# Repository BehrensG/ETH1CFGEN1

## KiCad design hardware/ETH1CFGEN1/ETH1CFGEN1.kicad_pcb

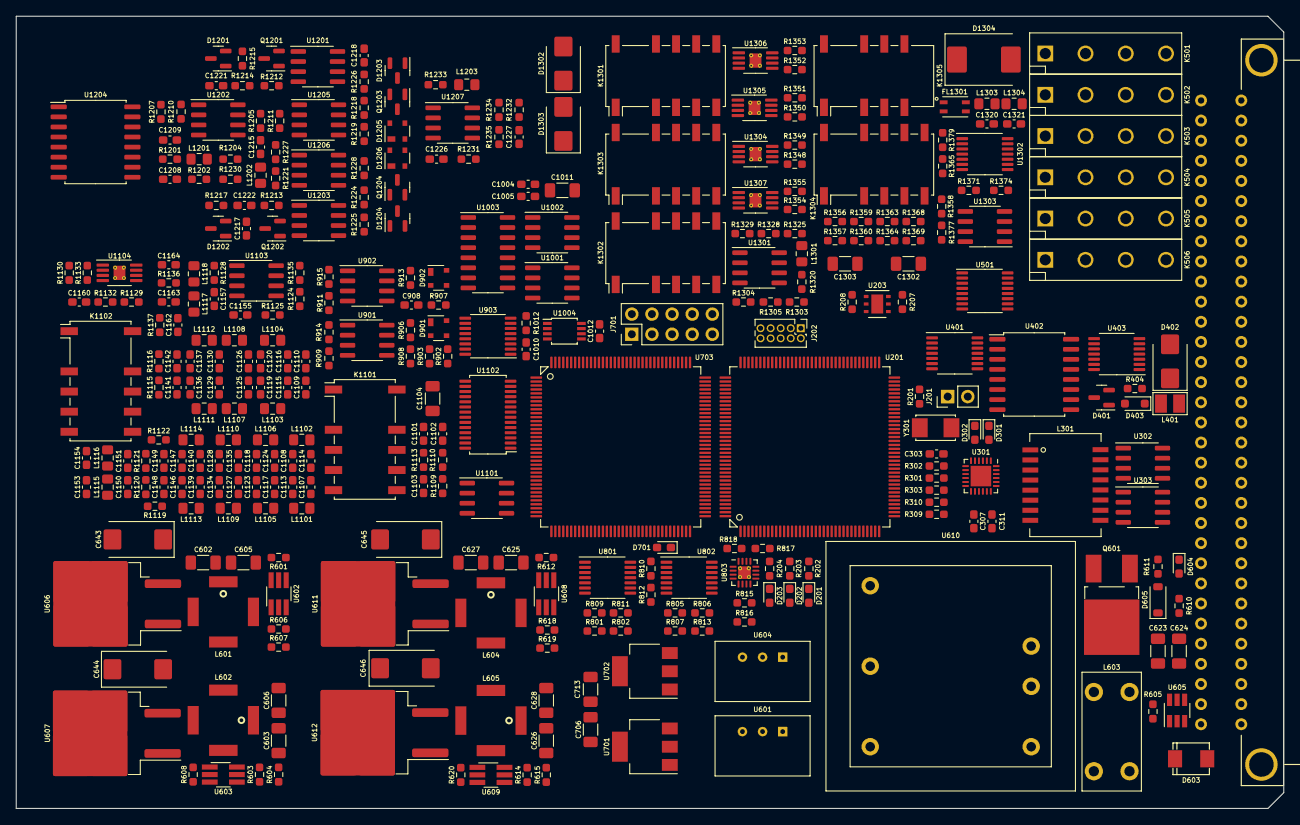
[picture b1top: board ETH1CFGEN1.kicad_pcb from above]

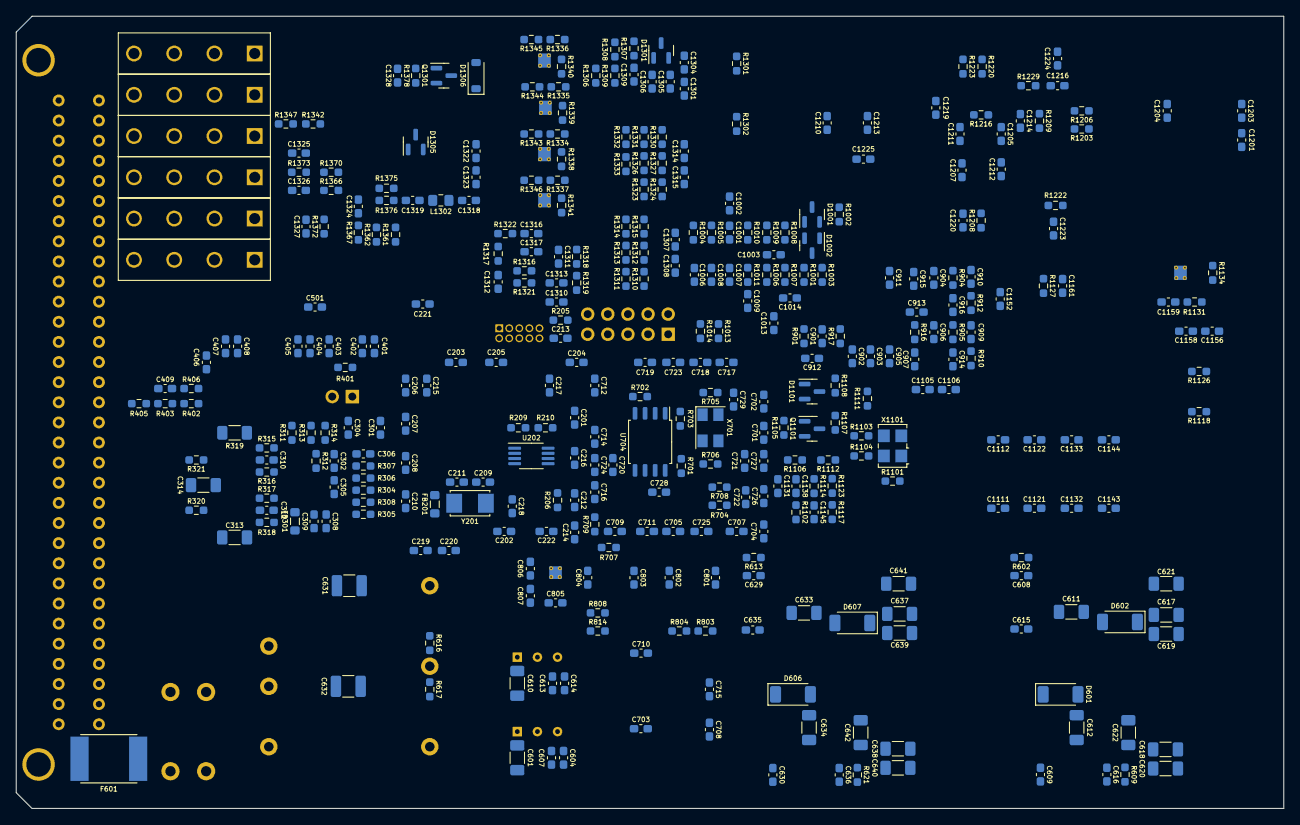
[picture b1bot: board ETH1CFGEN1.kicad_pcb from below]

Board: 6 copper layers, 160.0 x 100.0 mm, 693 parts (353 on the bottom side), 391 nets, no tracks yet.

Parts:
C201, C202, C203, C204, C205, C206, C207, C208, C210, C212, C213, C214, C216, C221, C222, C302, C305, C308, C309, C310, C311, C312, C401, C403, C404, C406, C408, C607, C614, C701, C702, C703, C704, C705, C707, C708, C709, C710, C711, C712, C714, C715, C716, C717, C718, C719, C720, C721, C722, C723, C724, C725, C726, C727, C728, C729, C801, C802, C803, C804, C806, C905, C907, C908, C913, C914, C915, C916, C1001, C1002, C1003, C1007, C1012, C1013, C1014, C1103, C1131, C1138, C1201, C1203, C1204, C1205, C1207, C1210, C1211, C1212, C1213, C1216, C1217, C1218, C1220, C1223, C1224, C1305, C1306, C1324, C1325, C1326, C1327: 100n; C_0603_1608Metric_Pad1.08x0.95mm_HandSolder
C209, C211, C301, C304: 8p; C_0603_1608Metric_Pad1.08x0.95mm_HandSolder
C215, C217: 2u2; C_0603_1608Metric_Pad1.08x0.95mm_HandSolder
C218, C219, C220, C306, C307, C402, C405, C407, C501, C604, C608, C609, C613, C629, C630, C805, C807, C1312, C1313, C1316: 1u; C_0603_1608Metric_Pad1.08x0.95mm_HandSolder
C303, C1004: 470p; C_0603_1608Metric_Pad1.08x0.95mm_HandSolder
C313, C314: 1n/1kV; C_1206_3216Metric_Pad1.33x1.80mm_HandSolder
C409, C1150, C1151, C1161: 47p; C_0603_1608Metric_Pad1.08x0.95mm_HandSolder
C601, C610: 1u/50V; C_1206_3216Metric_Pad1.33x1.80mm_HandSolder
C602, C603, C625, C626: 10u/50V; C_1206_3216Metric_Pad1.33x1.80mm_HandSolder
C605, C606, C617, C618, C619, C620, C623, C624, C627, C628, C639: 4u7/50V; C_1206_3216Metric_Pad1.33x1.80mm_HandSolder
C611, C612, C633, C634: 1u/HC; C_1206_3216Metric_Pad1.33x1.80mm_HandSolder
C615, C616, C635, C636: 4p7; C_0603_1608Metric_Pad1.08x0.95mm_HandSolder
C621, C622: 10u/35V; C_1206_3216Metric_Pad1.33x1.80mm_HandSolder
C631, C632: 330p/2kV; C_1210_3225Metric_Pad1.33x2.70mm_HandSolder
C637, C638, C640: 4u7/25V; C_1206_3216Metric_Pad1.33x1.80mm_HandSolder
C641, C642: 10u/25V; C_1206_3216Metric_Pad1.33x1.80mm_HandSolder
C643, C644, C645, C646: 22u/35V; CP_EIA-7343-31_Kemet-D_Pad2.25x2.55mm_HandSolder
C706, C713, C1104, C1302, C1303: 10u; C_1206_3216Metric_Pad1.33x1.80mm_HandSolder
C901, C912: 150n; C_0603_1608Metric_Pad1.08x0.95mm_HandSolder
C902, C903, C904, C906, C1145, C1152, C1221, C1222: 220n; C_0603_1608Metric_Pad1.08x0.95mm_HandSolder
C909, C910, C1008: 1000p; C_0603_1608Metric_Pad1.08x0.95mm_HandSolder
C911, C1317: 10n; C_0603_1608Metric_Pad1.08x0.95mm_HandSolder
C1005, C1136, C1137: 330p; C_0603_1608Metric_Pad1.08x0.95mm_HandSolder
C1006: 220p; C_0603_1608Metric_Pad1.08x0.95mm_HandSolder
C1009, C1125, C1126, C1164: 150p; C_0603_1608Metric_Pad1.08x0.95mm_HandSolder
C1010, C1208, C1214, C1215: 4700p; C_0603_1608Metric_Pad1.08x0.95mm_HandSolder
C1011: 2u2; C_1206_3216Metric_Pad1.33x1.80mm_HandSolder
C1101, C1102, C1107, C1108, C1111, C1112, C1121, C1122, C1132, C1133, C1143, C1144, C1163: 33p; C_0603_1608Metric_Pad1.08x0.95mm_HandSolder
C1105, C1106, C1146, C1147, C1156, C1158, C1301, C1304, C1307, C1308, C1314, C1315, C1322, C1323: 100p; C_0603_1608Metric_Pad1.08x0.95mm_HandSolder
C1109, C1110: 30p; C_0603_1608Metric_Pad1.08x0.95mm_HandSolder
C1113, C1114, C1117, C1118, C1123, C1124, C1141, C1142: 56p; C_0603_1608Metric_Pad1.08x0.95mm_HandSolder
C1115, C1116, C1319: 3p3; C_0603_1608Metric_Pad1.08x0.95mm_HandSolder
C1119, C1120: 120p; C_0603_1608Metric_Pad1.08x0.95mm_HandSolder
C1127, C1128, C1227: 62p; C_0603_1608Metric_Pad1.08x0.95mm_HandSolder
C1129, C1130: 8p2; C_0603_1608Metric_Pad1.08x0.95mm_HandSolder
C1134, C1135: 130p; C_0603_1608Metric_Pad1.08x0.95mm_HandSolder
C1139, C1140, C1162: 15p; C_0603_1608Metric_Pad1.08x0.95mm_HandSolder
C1148, C1149, C1226: 5p6; C_0603_1608Metric_Pad1.08x0.95mm_HandSolder
C1153, C1154, C1225: 22p; C_0603_1608Metric_Pad1.08x0.95mm_HandSolder
C1155, C1159, C1160, C1219: 10p; C_0603_1608Metric_Pad1.08x0.95mm_HandSolder
C1157: 1p; C_0603_1608Metric_Pad1.08x0.95mm_HandSolder
C1209: 3300p; C_0603_1608Metric_Pad1.08x0.95mm_HandSolder
C1309, C1310, C1311, C1328: 1n; C_0603_1608Metric_Pad1.08x0.95mm_HandSolder
C1318: 27p; C_0603_1608Metric_Pad1.08x0.95mm_HandSolder
C1320, C1321: 18p; C_0603_1608Metric_Pad1.08x0.95mm_HandSolder
D201, D701: BLUE; LED_0603_1608Metric_Pad1.05x0.95mm_HandSolder
D202, D604: RED; LED_0603_1608Metric_Pad1.05x0.95mm_HandSolder
D203, D302: GREEN; LED_0603_1608Metric_Pad1.05x0.95mm_HandSolder
D301: YELLOW; LED_0603_1608Metric_Pad1.05x0.95mm_HandSolder
D401, D1001, D1002, D1203, D1204, D1301, D1305: BAV99; SOT-23
D402: SMBJ5.0A; D_SMB
D403: SD36C-01FTG; D_SOD-323_HandSoldering
D601, D602, D606, D607: PMEG6010EP,115; D_SOD-128
D603: SM6T30AY; DO_214AA_REV
D605: MMSZ5249B; D_SOD-123
D901, D902, D1205, D1206: BAS40-07-E6327; SOT-143
D1101: BAS40-04; SOT-23
D1201, D1202: BZX84C3V0; SOT-23
D1302, D1303: SZ1SMB5918BT3G; D_SMB
D1304: SMCJ43CA; D_SMC
D1306: 1N4148; D_SOD-123
F601: MF-LSMF185/33X; Fuse_SMD2920
FB201, FB301: 742792031; L_0805_2012Metric_Pad1.05x1.20mm_HandSolder
FL1301: ACP3225-102-2P-T000; ACP3225
J201: Conn_02x01; PinHeader_1x02_P2.54mm_Vertical
J202: 20021111-00010T4LF; PinHeader_2x05_P1.27mm_Vertical
J501: C64AC; Socket_DIN41612-CaseC1-AC-Male-64Pin-2rows
J701: Conn_02x05_Odd_Even; PinHeader_2x05_P2.54mm_Vertical
K501, K502, K503, K504, K505, K506: HE3621A0510; HE360_x-5050462-8
K1101, K1102, K1301, K1302, K1303, K1304: G6SU-2F-DC3; Relay_DPDT_Omron_G6SK-2F
K1305: TX2SA-4.5V; Relay_DPDT_Omron_G6S-2F
L301: 749010012A
L401: CW252016-R33G; CW252016
L601, L602, L604, L605: 74489440068
L603: 7448014501
L1101, L1102, L1103, L1104, L1105, L1106: 470n; L_0805_2012Metric_Pad1.15x1.40mm_HandSolder
L1107, L1108: 680n; L_0805_2012Metric_Pad1.15x1.40mm_HandSolder
L1109, L1110: 560n; L_0805_2012Metric_Pad1.15x1.40mm_HandSolder
L1111, L1112: 910n; L_0805_2012Metric_Pad1.15x1.40mm_HandSolder
L1113, L1114: 750n; L_0805_2012Metric_Pad1.15x1.40mm_HandSolder
L1115, L1116: 1u; L_0805_2012Metric_Pad1.15x1.40mm_HandSolder
L1117: 1u2; L_0805_2012Metric_Pad1.15x1.40mm_HandSolder
L1118: 100n; L_0805_2012Metric_Pad1.15x1.40mm_HandSolder
L1201, L1301: 1m; L_0805_2012Metric_Pad1.15x1.40mm_HandSolder
L1202, L1203: 82n; L_0805_2012Metric_Pad1.15x1.40mm_HandSolder
L1302: 180n; L_0805_2012Metric_Pad1.15x1.40mm_HandSolder
L1303, L1304: 47n; L_0805_2012Metric_Pad1.15x1.40mm_HandSolder
Q601: IRFR5410; TO-252-2_Rectifier
Q1101, Q1203: MMBT5087LT1G; SOT-23
Q1201: MMBF4416A; SOT-23
Q1202: MMBFJ175LT1; SOT-23
Q1204: MMBT6429LT1; SOT-23
Q1301: 2N7002; SOT-23
R201, R205, R206, R303, R306, R307, R308, R309, R311, R401, R701, R702, R709, R913, R916, R1001, R1002, R1003, R1004, R1005, R1006, R1007, R1013, R1102, R1117, R1123, R1127, R1203, R1206, R1210, R1225, R1226, R1232, R1303, R1319, R1377, R1378: 10k; R_0603_1608Metric_Pad0.98x0.95mm_HandSolder
R202, R204: 680; R_0603_1608Metric_Pad0.98x0.95mm_HandSolder
R203: 560; R_0603_1608Metric_Pad0.98x0.95mm_HandSolder
R207, R208, R209, R210, R704, R708, R817, R818: 4k7; R_0603_1608Metric_Pad0.98x0.95mm_HandSolder
R301, R302, R304, R305: 33; R_0603_1608Metric_Pad0.98x0.95mm_HandSolder
R310: 1k5; R_0603_1608Metric_Pad0.98x0.95mm_HandSolder
R312: 12k1; R_0603_1608Metric_Pad0.98x0.95mm_HandSolder
R313, R314: 270; R_0603_1608Metric_Pad0.98x0.95mm_HandSolder
R315, R316, R317, R318: 49R9; R_0603_1608Metric_Pad0.98x0.95mm_HandSolder
R319: 1M/1kV; R_1206_3216Metric_Pad1.30x1.75mm_HandSolder
R320, R321: 75/1%; R_0603_1608Metric_Pad0.98x0.95mm_HandSolder
R402: 14k7; R_0603_1608Metric_Pad0.98x0.95mm_HandSolder
R403, R1105, R1115, R1116, R1119, R1122, R1125, R1212, R1213, R1220, R1222: 100; R_0603_1608Metric_Pad0.98x0.95mm_HandSolder
R404, R705, R809, R810, R811, R812, R902, R903, R904, R905, R907, R917, R1014, R1101, R1107, R1114, R1207, R1308: 1k; R_0603_1608Metric_Pad0.98x0.95mm_HandSolder
R405: 47; R_0603_1608Metric_Pad0.98x0.95mm_HandSolder
R406, R1103, R1104, R1128, R1135, R1342, R1347: 51R1; R_0603_1608Metric_Pad0.98x0.95mm_HandSolder
R601, R603, R606, R608, R612, R614, R618, R620: 1M; R_0603_1608Metric_Pad0.98x0.95mm_HandSolder
R602, R604, R613, R615: 287k; R_0603_1608Metric_Pad0.98x0.95mm_HandSolder
R605, R914, R915, R1131, R1134, R1204, R1218, R1231, R1304, R1307, R1358, R1362, R1365, R1366: 100k; R_0603_1608Metric_Pad0.98x0.95mm_HandSolder
R607: 97k6; R_0603_1608Metric_Pad0.98x0.95mm_HandSolder
R609, R1379: 46k4; R_0603_1608Metric_Pad0.98x0.95mm_HandSolder
R610: 6k8; R_0603_1608Metric_Pad0.98x0.95mm_HandSolder
R611: 370; R_0603_1608Metric_Pad0.98x0.95mm_HandSolder
R616, R617: OPT; R_0603_1608Metric_Pad0.98x0.95mm_HandSolder
R619, R802, R806: 249k; R_0603_1608Metric_Pad0.98x0.95mm_HandSolder
R621: 111k; R_0603_1608Metric_Pad0.98x0.95mm_HandSolder
R703: 2k2; R_0603_1608Metric_Pad0.98x0.95mm_HandSolder
R706: 27; R_0603_1608Metric_Pad0.98x0.95mm_HandSolder
R707: 1K; R_0603_1608Metric_Pad0.98x0.95mm_HandSolder
R801, R805, R813: 33k; R_0603_1608Metric_Pad0.98x0.95mm_HandSolder
R803, R804, R807, R808, R814: 49k9; R_0603_1608Metric_Pad0.98x0.95mm_HandSolder
R815, R901, R1216: 0; R_0603_1608Metric_Pad0.98x0.95mm_HandSolder
R816: DNP; R_0603_1608Metric_Pad0.98x0.95mm_HandSolder
R906, R908: 1k96; R_0603_1608Metric_Pad0.98x0.95mm_HandSolder
R909, R911: 24k9; R_0603_1608Metric_Pad0.98x0.95mm_HandSolder
R910, R912: 33k2; R_0603_1608Metric_Pad0.98x0.95mm_HandSolder
R1008, R1010, R1011: 6k81; R_0603_1608Metric_Pad0.98x0.95mm_HandSolder
R1009: 237k; R_0603_1608Metric_Pad0.98x0.95mm_HandSolder
R1012, R1209, R1211: 619; R_0603_1608Metric_Pad0.98x0.95mm_HandSolder
R1106: 82k5; R_0603_1608Metric_Pad0.98x0.95mm_HandSolder
R1108: 2k; R_0603_1608Metric_Pad0.98x0.95mm_HandSolder
R1109, R1113: 69; R_0603_1608Metric_Pad0.98x0.95mm_HandSolder
R1110, R1111: 261; R_0603_1608Metric_Pad0.98x0.95mm_HandSolder
R1112, R1301, R1302: 21k5; R_0603_1608Metric_Pad0.98x0.95mm_HandSolder
R1118, R1126: 1k78; R_0603_1608Metric_Pad0.98x0.95mm_HandSolder
R1120, R1121: 511; R_0603_1608Metric_Pad0.98x0.95mm_HandSolder
R1124, R1219, R1223, R1224, R1228, R1338, R1339, R1340, R1341, R1356, R1357, R1359, R1360, R1363, R1364, R1368, R1369: 21R5; R_0603_1608Metric_Pad0.98x0.95mm_HandSolder
R1129, R1130: 200; R_0603_1608Metric_Pad0.98x0.95mm_HandSolder
R1132, R1133: 953; R_0603_1608Metric_Pad0.98x0.95mm_HandSolder
R1136, R1235, R1306, R1309: 34R8; R_0603_1608Metric_Pad0.98x0.95mm_HandSolder
R1137: 196; R_0603_1608Metric_Pad0.98x0.95mm_HandSolder
R1201: 348; R_0603_1608Metric_Pad0.98x0.95mm_HandSolder
R1202, R1334, R1335, R1336, R1337: 178; R_0603_1608Metric_Pad0.98x0.95mm_HandSolder
R1205: 1k47; R_0603_1608Metric_Pad0.98x0.95mm_HandSolder
R1208, R1215: 2k05; R_0603_1608Metric_Pad0.98x0.95mm_HandSolder
R1214, R1217: 5k11; R_0603_1608Metric_Pad0.98x0.95mm_HandSolder
R1221, R1227, R1233, R1234: 316; R_0603_1608Metric_Pad0.98x0.95mm_HandSolder
R1229, R1230: 500; R_0603_1608Metric_Pad0.98x0.95mm_HandSolder
R1305: 12k4; R_0603_1608Metric_Pad0.98x0.95mm_HandSolder
R1310, R1311, R1314, R1315, R1323, R1324, R1330, R1331, R1332, R1333: 383; R_0603_1608Metric_Pad0.98x0.95mm_HandSolder
R1312, R1313, R1326, R1327: 287; R_0603_1608Metric_Pad0.98x0.95mm_HandSolder
R1316: 45k3; R_0603_1608Metric_Pad0.98x0.95mm_HandSolder
R1317, R1318, R1320, R1321: 10; R_0603_1608Metric_Pad0.98x0.95mm_HandSolder
R1322: 31R6; R_0603_1608Metric_Pad0.98x0.95mm_HandSolder
R1325, R1328, R1329: 162; R_0603_1608Metric_Pad0.98x0.95mm_HandSolder
R1343, R1344, R1345, R1346: 909; R_0603_1608Metric_Pad0.98x0.95mm_HandSolder
R1348, R1349, R1350, R1351, R1352, R1353, R1354, R1355: 56R2; R_0603_1608Metric_Pad0.98x0.95mm_HandSolder
R1361: 3k48; R_0603_1608Metric_Pad0.98x0.95mm_HandSolder
R1367, R1372: 59k; R_0603_1608Metric_Pad0.98x0.95mm_HandSolder
R1370, R1371: 215k; R_0603_1608Metric_Pad0.98x0.95mm_HandSolder
R1373, R1374: 5k62; R_0603_1608Metric_Pad0.98x0.95mm_HandSolder
R1375: 30k1; R_0603_1608Metric_Pad0.98x0.95mm_HandSolder
R1376: 19k6; R_0603_1608Metric_Pad0.98x0.95mm_HandSolder
U201: STM32H723ZGTx; TQFP-144_20x20mm_P0.5mm
U202: 24LC08B-E/MS; MSOP-8_3x3mm_P0.65mm
U203: HDC1080; Texas_PWSON-N6
U301: LAN8742; QFN-24-1EP_4x4mm_P0.5mm_EP2.6x2.6mm
U302, U303: LC03-3.3BTG; SOIC-8_3.9x4.9mm_P1.27mm
U401: TXB0104PW; TSSOP-14_4.4x5mm_P0.65mm
U402: ADuM5402; SOIC-16W_7.5x10.3mm_P1.27mm
U403: 74AC125; TSSOP-14_4.4x5mm_P0.65mm
U501: ULN2003AIPWR; TSSOP-16_4.4x5mm_P0.65mm
U601: TSR1-2450; TSR1
U602, U603, U608, U609: LT8330ES6#TRMPBF; TSOT-23-6_HandSoldering
U604: TSR1-2433; TSR1
U605: MAX5902AAEUT+T; SOT-23-6_Handsoldering
U606: MC7815BD2TR4G; TO-263-2
U607: MC7915ACD2TG; TO-263-2
U610: THL15-2415WI; THL15
U611: MC7805CD2TG; TO-263-2
U612: L7905CD2T-TR; TO-263-2
U701: TLV1117LV33DCYR; SOT-223-3_TabPin2
U702: TLV1117LV12DCYR; SOT-223-3_TabPin2
U703: XC6SLX9-3TQG144I; TQFP-144_20x20mm_P0.5mm
U704: W25Q64JV; SOIC-8_5.23x5.23mm_P1.27mm
U801, U802: TL074HIPWR; TSSOP-14_4.4x5mm_P0.65mm
U803: TLA2528IRTER; WQFN-16-1EP_3x3mm_P0.5mm_EP1.6x1.6mm_ThermalVias
U901, U902, U1001, U1002, U1301, U1303: TL072CD; SOIC-8_3.9x4.9mm_P1.27mm
U903: DAC8568IBPW; TSSOP-16_4.4x5mm_P0.65mm
U1003: DG408DY-T1-E3; SOIC-16_3.9x9.9mm_P1.27mm
U1004: ADS7818EB; TSSOP-8_3x3mm_P0.65mm
U1101: TL072CDT; SOIC-8_3.9x4.9mm_P1.27mm
U1102: AD9744; TSSOP-28_4.4x9.7mm_P0.65mm
U1103: LT1016CS8; SOIC-8_3.9x4.9mm_P1.27mm
U1104, U1304, U1305, U1306, U1307: THS3001IDG; MSOP-8-1EP_3x3mm_P0.65mm_EP1.5x1.8mm_ThermalVias
U1201, U1202, U1203: AD706ARZ; SOIC-8_3.9x4.9mm_P1.27mm
U1204: AD1851RZ; SOIC-16W_7.5x10.3mm_P1.27mm
U1205: AD8180ARZ; SOIC-8_3.9x4.9mm_P1.27mm
U1206, U1207: AD8009AR; SOIC-8_3.9x4.9mm_P1.27mm
U1302: LMV339IPWR; TSSOP-14_4.4x5mm_P0.65mm
X701: ASFL1-100.000MHZ-L-T; Crystal_SMD_5032-4Pin_5.0x3.2mm
X1101: SG5032CAN 50.000000M-TJGA3; Oscillator_SMD_SeikoEpson_SG8002LB-4Pin_5.0x3.2mm
Y201: NX5032GA-16.000M; NX5032GA
Y301: NX5032GA-25.000000MHZ-LN-CD-1; NX5032GA

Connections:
+2V5: R901.1, R909.1, R911.1, R1003.2, R1004.1, R1009.2, R1117.1, R1208.1, R1303.1, U1002.1, U1002.2 (-), U1302.11 (+)
+3.3V: C201.1, C202.1, C203.1, C204.1, C205.1, C206.1, C207.1, C208.1, C210.1, C212.1, C214.1, C216.1, C218.1, C221.2, C222.2, C302.1, C305.1, C401.1, C402.1, C613.1, C614.1, C806.2, C912.2, D201.2 (A), D202.2 (A), D203.2 (A), D1101.2, FB201.2, FB301.2, J202.1, R201.2, R205.1, R207.1, R208.1, R209.1, R210.1, R306.1, R307.1, R308.1, R309.1, R310.1, R401.1, R817.1, R818.1, R1101.1, R1107.2, U201.6 (VBAT), U201.17 (VDD), U201.30 (VDD), U201.39 (VDD), U201.52 (VDD), U201.62 (VDD), U201.72 (VDD), U201.84 (VDD), U201.95 (VDD33USB), U201.108 (VDD), U201.121 (VDD), U201.131 (VDD), U201.143 (PDR_ON), U201.144 (VDD), U202.8 (VCC), U203.5 (VCC), U301.9 (VDDIO), U401.1 (VCCA), U604.3 (VO), U802.3 (+), U803.10 (DVDD), U903.3 (AVDD), U1102.24 (AVDD), U1102.27 (DVDD), X1101.4 (VCC)
+5V: C403.1, C404.1, C405.1, C641.1, C645.1, C805.2, C1012.1, C1201.1, C1204.1, C1205.1, C1207.1, C1210.1, D1306.1 (K), K1305.1, R805.2, R1002.1, R1013.1, U401.14 (VCCB), U402.1 (VDD1), U611.3 (OUT), U803.7 (AVDD), U1004.8 (VDD), U1103.1 (V+), U1204.3 (+Vl), U1204.16 (+VS), U1205.4 (+VS), U1206.7 (V+), U1207.7 (V+)
+5VD: C501.1, C604.1, C607.1, C703.1, K501.2, K502.2, K503.2, K504.2, K505.2, K506.2, R813.2, U501.9 (COM), U601.3 (VO), U701.3 (VI)
+5VP: C406.1, C407.1, C408.1, R404.1, U402.10 (VSEL), U402.16 (VISO), U403.14 (VCC)
+15V: C621.1, C643.1, C801.2, C803.2, C913.1, C915.1, C1002.1, C1007.1, C1303.1, D1001.1 (K), D1001.3 (K), D1305.2 (A), R806.2, R1112.2, R1301.1, R1366.1, U606.3 (OUT), U801.4 (V+), U802.4 (V+), U901.8 (V+), U902.8 (V+), U1001.8 (V+), U1002.8 (V+), U1101.8 (V+), U1104.7 (V+), U1201.8 (V+), U1202.8 (V+), U1203.8 (V+), U1301.8 (V+), U1302.3 (V+), U1303.8 (V+), U1304.7 (V+), U1305.7 (V+), U1306.7 (V+), U1307.7 (V+)
+24V: F601.2, J501.A31 (31A), J501.A32 (32A), J501.C31 (31C), J501.C32 (32C)
-2V5: C1001.2, R1005.2, R1006.2, U1002.7, U1302.8 (-)
-5V: C642.1, C646.2, C1203.1, C1211.1, C1212.1, C1213.1, R801.2, U612.3 (VO), U1103.4 (V-), U1204.1 (-Vs), U1205.5 (-VS), U1206.4 (V-), U1207.4 (V-)
-15V: C622.1, C644.2, C802.2, C804.2, C914.1, C916.1, C1003.1, C1014.1, C1302.1, D1002.2 (A), D1002.3 (K), D1305.1 (K), Q1101.3 (C), R802.2, R1302.2, R1365.1, U607.3 (VO), U801.11 (V-), U802.11 (V-), U901.4 (V-), U902.4 (V-), U1001.4 (V-), U1002.4 (V-), U1101.4 (V-), U1104.4 (V-), U1104.9 (THR), U1201.4 (V-), U1202.4 (V-), U1203.4 (V-), U1301.4 (V-), U1302.12 (V-), U1303.4 (V-), U1304.4 (V-), U1304.9 (THR), U1305.4 (V-), U1305.9 (THR), U1306.4 (V-), U1306.9 (THR), U1307.4 (V-), U1307.9 (THR)
/ADC/+1.25VREF: R1001.1, R1003.1, U1003.11 (S5)
/Connector/A: J501.A2 (2A), J501.C2 (2C), K501.4
/Connector/B: J501.A3 (3A), J501.C3 (3C), K502.4
/Connector/C: J501.A4 (4A), J501.C4 (4C), K503.4
/Connector/CXN_REL1: U201.88 (PG3), U501.1 (I1)
/Connector/CXN_REL2: U201.89 (PG4), U501.2 (I2)
/Connector/CXN_REL3: U201.90 (PG5), U501.3 (I3)
/Connector/CXN_REL4: U201.91 (PG6), U501.4 (I4)
/Connector/CXN_REL5: U201.92 (PG7), U501.5 (I5)
/Connector/CXN_REL6: U201.93 (PG8), U501.6 (I6)
/Connector/D: J501.A5 (5A), J501.C5 (5C), K504.4
/Connector/E: J501.A6 (6A), J501.C6 (6C), K505.4
/Connector/EXT_TRIG: C409.1, D403.1 (A1), J501.A16 (16A), L401.1
/Connector/F: J501.A7 (7A), J501.C7 (7C), K506.4
/Connector/MAIN_OUTPUT: C1321.1, D1304.2 (A2), K501.1, K502.1, L1304.2
/Connector/RX+: J501.A20 (20A), U303.8
/Connector/RX-: J501.A21 (21A), U303.5
/Connector/TX+: J501.C20 (20C), U302.8
/Connector/TX-: J501.C21 (21C), U302.5
/DAC/V_AMPL: C905.2, R916.1, U901.6 (-), U901.7
/DAC/V_NEDGE: C903.1, R903.2
/DAC/V_NULL_SINE: C909.2, R914.2, U901.1
/DAC/V_NULL_SQ: C910.2, R915.2, U902.1
/DAC/V_OFFSET: C911.1, R913.2
/DAC/V_PEDGE: C902.1, R902.2
/Ethernet/ETH_RXN: L301.8 (RD-), R318.2, U301.22 (RXN)
/Ethernet/ETH_RXP: L301.6 (RD+), R317.2, U301.23 (RXP)
/Ethernet/ETH_TXN: L301.3 (TD-), R316.2, U301.20 (TXN)
/Ethernet/ETH_TXP: L301.1 (TD+), R315.2, U301.21 (TXP)
/Ethernet/MDIO: R310.2, U201.36 (PA2), U301.12 (MDIO)
/Ethernet/MODE0: R301.1, R306.2, U301.8 (RXD0/MODE0)
/Ethernet/MODE1: R302.1, R307.2, U301.7 (RXD1/MODE1)
/Ethernet/MODE2: R304.1, R308.2, U301.11 (CRS_DV/MODE2)
/Ethernet/REFCLK0: R305.1, R309.2, U301.14 (~INT/REFCLK0)
/Ethernet/REF_CLK: R305.2, U201.35 (PA1)
/Ethernet/RMII_CRS_DV: R304.2, U201.43 (PA7)
/Ethernet/RMII_MDC: U201.27 (PC1), U301.13 (MDC)
/Ethernet/RMII_RXD0: R301.2, U201.44 (PC4)
/Ethernet/RMII_RXD1: R302.2, U201.45 (PC5)
/Ethernet/RMII_TXD0: U201.128 (PG13), U301.17 (TXD0)
/Ethernet/RMII_TXD1: U201.74 (PB13), U301.18 (TXD1)
/Ethernet/RMII_TXEN: U201.126 (PG11), U301.16 (TXEN)
/FPGA/CMPCS_B_2: R709.1, U703.72 (CMPCS_B_2)
/FPGA/DONE_2: R707.1, U703.71 (DONE_2)
/FPGA/FLASH_HOLD: R701.2, U704.7 (IO3)
/FPGA/FLASH_INIT_B: R704.2, U703.39 (IO_L65P_INIT_B_2)
/FPGA/FLASH_SCK: U703.70 (IO_L1P_CCLK_2), U704.6 (CLK)
/FPGA/FLASH_WP: R702.2, U704.3 (IO2)
/FPGA/FLASH_nCS: R703.2, U703.38 (IO_L65N_CSO_B_2), U704.1 (~CS)
/FPGA/FPGA_TCK: J701.6, U703.109 (TCK)
/FPGA/FPGA_TDI: J701.10, U703.110 (TDI)
/FPGA/FPGA_TDO: J701.8, U703.106 (TDO)
/FPGA/FPGA_TMS: J701.4, U703.107 (TMS)
/FPGA/PROG_B_2: R708.1, U703.37 (PROGRAM_B_2)
/MCU/EEPROM_WP: U201.135 (PB5), U202.7 (WP)
/MCU/I2C1_SCL: R207.2, R210.2, U201.136 (PB6), U202.6 (SCL), U203.6 (SCL)
/MCU/I2C1_SDA: R208.2, R209.2, U201.137 (PB7), U202.5 (SDA), U203.1 (SDA)
/MCU/I2C2_SCL: R817.2, U201.11 (PF1), U803.13 (SCL)
/MCU/I2C2_SDA: R818.2, U201.10 (PF0), U803.14 (SDA)
/MCU/LED_BLUE: R202.1, U201.142 (PE1)
/MCU/LED_GREEN: R204.1, U201.46 (PB0)
/MCU/LED_RED: R203.1, U201.75 (PB14)
/MCU/MCU_DEFAULT: J201.1, R201.1, U201.76 (PB15)
/MCU/NRST: C213.1, J202.10, R205.2, U201.25 (NRST), U301.15 (~RST)
/MCU/TCK_SWCLK: J202.4, U201.109 (PA14(JTCK)
/MCU/TMS_SWDIO: J202.2, U201.105 (PA13(JTMS)
/MCU/TRIG_EN: U201.102 (PA10), U401.2 (A1)
/MCU/TRIG_IN: U201.100 (PA8), U401.4 (A3)
/MCU/TRIG_OUT: U201.101 (PA9), U401.3 (A2)
/Output/MEAS_BUF: C1309.1, R1307.2
/Output/MEAS_OUT: C1328.1, R1378.2
/Output/OUTPUT: FL1301.1, K1305.8
/Output/RST_+20DB: C1322.1, K1304.12
/Output/RST_-10DB: C1308.2, K1302.1
/Output/RST_-20DB: C1315.2, K1303.1
/Output/SET_+20DB: C1323.2, K1304.1
/Output/SET_-10DB: C1307.1, K1302.12
/Output/SET_-20DB: C1314.1, K1303.12
/Output/SET_SIN_ARB: C1304.2, K1301.12
/Output/SET_SQ_PLS: C1301.1, K1301.1
/Self test/AIN0: U802.1, U802.2 (-), U803.15 (AIN0/GPIO0)
/Self test/AIN1: U802.6 (-), U802.7, U803.16 (AIN1/GPIO1)
/Self test/AIN2: R811.1, U801.1, U803.1 (AIN2/GPIO2)
/Self test/AIN3: U802.8, U802.9 (-), U803.2 (AIN3/GPIO3)
/Self test/AIN4: U802.13 (-), U802.14, U803.3 (AIN4/GPIO4)
/Self test/AIN5: R812.1, U801.8, U803.4 (AIN5/GPIO5)
/Square/SQ_PLS: C1227.1, R1235.2
/Trigger/EXT_TRIG_SIGN: R402.1, U402.12 (VIC), U403.3 (O)
/Trigger/TRIG_OUT_EN: U402.14 (VOA), U403.4 (EN), U403.10 (EN), U403.13 (EN)
/Trigger/TRIG_OUT_SIGN: U402.13 (VOB), U403.5 (D), U403.9 (D), U403.12 (D)
/WaveformDAC/SET_ARB_FLTR1: C1105.1, K1101.12
/WaveformDAC/SET_ARB_FLTR2: C1156.1, K1102.1
/WaveformDAC/SET_SIN_FLTR1: C1106.2, K1101.1
/WaveformDAC/SET_SIN_FLTR2: C1158.2, K1102.12
/WaveformDAC/SINE_ARB: C1164.1, L1118.2
/WaveformDAC/V_AMPL: D1101.3, R1102.1, U1102.17 (REFIO)
/WaveformDAC/V_DTY_CYCL: C1131.1, C1138.1, R1114.1
/WaveformDAC/WFDAC_CLK: R1103.2, U1102.28 (CLK)
Earth: C313.1, C314.2, J501.A18 (18A), J501.A22 (22A), J501.C18 (18C), J501.C22 (22C), R319.1
FPGA_1V2: C713.1, C715.1, C723.1, C724.1, C725.1, C726.1, C727.1, U702.2 (VO), U703.19 (VCCINT), U703.28 (VCCINT), U703.52 (VCCINT), U703.89 (VCCINT), U703.128 (VCCINT)
FPGA_3V3: C701.1, C702.1, C704.1, C705.1, C706.1, C707.1, C708.1, C709.1, C710.1, C711.1, C712.1, C714.1, C716.1, C717.1, C718.1, C719.1, C720.1, C721.1, C722.1, C728.1, C729.1, D701.2 (A), J701.2, R701.1, R702.1, R703.1, R704.1, R705.1, R708.2, R709.2, U701.2 (VO), U702.3 (VI), U703.4 (VCCO_3), U703.18 (VCCO_3), U703.20 (VCCAUX), U703.31 (VCCO_3), U703.36 (VCCAUX), U703.42 (VCCO_2), U703.53 (VCCAUX), U703.63 (VCCO_2), U703.69 (IO_L1N_M0_CMPMISO_2), U703.76 (VCCO_1), U703.86 (VCCO_1), U703.90 (VCCAUX), U703.103 (VCCO_1), U703.122 (VCCO_0), U703.125 (VCCO_0), U703.129 (VCCAUX), U703.135 (VCCO_0), U704.8 (VCC), X701.4 (VCC)
GND1: C406.2, C407.2, C408.2, D401.1 (K), D402.2 (A), D403.2 (A2), J501.C16 (16C), R406.2, U402.9 (GNDISO), U402.15 (GNDISO), U403.1 (EN), U403.7 (GND)
GNDA: C201.2, C202.2, C203.2, C204.2, C205.2, C206.2, C207.2, C208.2, C209.2, C210.2, C211.2, C212.2, C213.2, C214.2, C215.2, C216.2, C217.2, C218.2, C219.2, C220.2, C221.1, C222.1, C301.2, C302.2, C303.2, C304.2, C305.2, C306.2, C307.2, C308.2, C309.2, C310.2, C311.2, C312.2, C313.2, C401.2, C402.2, C403.2, C404.2, C405.2, C501.2, C601.2, C602.2, C603.2, C604.2, C605.2, C606.2, C607.2, C608.2, C609.2, C610.2, C613.2, C614.2, C617.2, C618.2, C619.2, C620.2, C621.2, C622.2, C625.2, C626.2, C627.2, C628.2, C629.2, C630.2, C632.1, C637.2, C638.2, C639.2, C640.2, C641.2, C642.2, C643.2, C644.1, C645.2, C646.1, C701.2, C702.2, C703.2, C704.2, C705.2, C706.2, C707.2, C708.2, C709.2, C710.2, C711.2, C712.2, C713.2, C714.2, C715.2, C716.2, C717.2, C718.2, C719.2, C720.2, C721.2, C722.2, C723.2, C724.2, C725.2, C726.2, C727.2, C728.2, C729.2, C801.1, C802.1, C803.1, C804.1, C805.1, C806.1, C807.1, C901.1, C902.2, C903.2, C904.2, C906.2, C907.2, C908.2, C911.2, C912.1, C913.2, C914.2, C915.2, C916.2, C1002.2, C1003.2, C1004.2, C1005.2, C1007.2, C1009.2, C1010.2, C1011.2, C1012.2, C1013.2, C1014.2, C1101.2, C1102.2, C1103.2, C1104.2, C1105.2, C1106.1, C1107.2, C1108.1, C1109.2, C1110.1, C1113.2, C1114.1, C1115.2, C1116.1, C1117.2, C1118.1, C1119.2, C1120.1, C1123.2, C1124.1, C1125.2, C1126.1, C1127.2, C1128.1, C1129.2, C1130.1, C1131.2, C1134.2, C1135.1, C1136.2, C1137.1, C1139.2, C1140.1, C1141.2, C1142.1, C1145.2, C1146.2, C1147.1, C1148.2, C1149.1, C1150.2, C1151.1, C1152.2, C1153.2, C1154.1, C1156.2, C1158.1, C1159.1, C1160.2, C1161.2, C1162.2, C1163.2, C1164.2, C1201.2, C1203.2, C1204.2, C1205.2, C1207.2, C1208.2, C1209.2, C1210.2, C1211.2, C1212.2, C1213.2, C1214.2, C1215.2, C1219.2, C1223.2, C1224.2, C1225.2, C1226.2, C1227.2, C1301.2, C1302.2, C1303.2, C1304.1, C1305.2, C1306.2, C1307.2, C1308.1, C1309.2, C1312.2, C1313.2, C1314.2, C1315.1, C1316.2, C1317.2, C1318.2, C1319.2, C1322.2, C1323.1, C1324.2, C1325.2, C1326.2, C1328.2, D601.1 (K), D606.1 (K), D1101.1, D1203.1 (K), D1204.2 (A), D1302.2 (A), D1303.1 (K), FL1301.2, J201.2, J202.3, J202.5, J701.1, J701.3, J701.5, J701.7, J701.9, K505.1, K506.1, K1301.5, K1305.3, K1305.4, K1305.5, L601.3, L604.3, L1115.2, L1116.1, L1202.2, L1203.2, Q1301.2 (S), R206.1, R303.2, R311.2, R312.1, R313.2, R314.2, R319.2, R602.2, R604.2, R607.2, R609.2, R613.2, R615.2, R617.2, R619.2, R621.2, R803.2, R804.2, R807.2, R808.2, R814.2, R816.1, R910.1, R912.1, R1001.2, R1108.1, R1115.2, R1116.1, R1120.2, R1121.1, R1132.2, R1202.1, R1203.1, R1207.2, R1215.1, R1216.1, R1218.1, R1231.1, R1304.2, R1305.2, R1310.1, R1311.1, R1314.2, R1315.2, R1323.1, R1324.1, R1330.2, R1331.2, R1332.2, R1333.2, R1334.1, R1335.1, R1336.1, R1337.1, R1367.2, R1373.2, R1374.2, R1376.2, U201.16 (VSS), U201.31 (VSSA), U201.38 (VSS), U201.51 (VSS), U201.61 (VSS), U201.83 (VSS), U201.94 (VSS), U201.107 (VSS), U201.120 (VSS), U201.130 (VSS), U202.1 (A0), U202.2 (A1), U202.3 (A2), U202.4 (GND), U203.2 (GND), U301.25 (VSS), U401.7 (GND), U402.2 (GND1), U402.8 (GND1), U501.8 (GND), U601.2 (GND), U602.2 (GND), U603.2 (GND), U604.2 (GND), U606.2 (GND), U607.1 (GND), U608.2 (GND), U609.2 (GND), U610.5 (-VOUT), U611.2 (GND), U612.1 (GND), U701.1 (GND), U702.1 (GND), U703.3 (GND), U703.13 (GND), U703.25 (GND), U703.49 (GND), U703.54 (GND), U703.60 (IO_L13P_M1_2), U703.68 (GND), U703.73 (SUSPEND), U703.77 (GND), U703.91 (GND), U703.96 (GND), U703.108 (GND), U703.113 (GND), U703.130 (GND), U703.136 (GND), U704.4 (GND), U801.3 (+), U801.10 (+), U803.9 (GND), U803.17 (PAD), U902.5 (+), U903.14 (GND), U1002.5 (+), U1003.4 (S0), U1003.14 (GND), U1004.3 (IN-), U1004.4 (GND), U1101.5 (+), U1102.20 (AGND), U1102.26 (DGND), U1103.6 (GND), U1204.2 (DGND), U1204.12 (AGND), U1205.2 (GND), U1303.3 (+), X701.2 (GND), X1101.2 (GND)
GNDPWR: C623.2, C624.2, D603.2 (A), D604.1 (K), J501.A27 (27A), J501.A28 (28A), J501.C27 (27C), J501.C28 (28C), L603.1, U605.4 (GND)
unnamed: C215.1, U201.71 (VCAP)
unnamed: C217.1, U201.106 (VCAP)
unnamed: C314.1, R320.2, R321.2
unnamed: C409.2, R406.1
unnamed: C905.1, R906.2, R908.1
unnamed: C908.1, D902.2, D902.4, R907.2, R913.1
unnamed: C1004.1, C1005.1, R1008.2, R1009.1, R1010.1
unnamed: C1006.2, C1008.2, R1010.2, R1011.1
unnamed: C1103.1, R1109.2, R1110.1, R1113.2
unnamed: C1104.1, R1110.2, R1111.1
unnamed: C1107.1, C1111.1, K1101.5, L1101.1
unnamed: C1108.2, C1112.1, K1101.8, L1102.1
unnamed: C1109.1, C1115.1, K1101.3, L1103.1
unnamed: C1110.2, C1116.2, K1101.10, L1104.1
unnamed: C1111.2, C1113.1, C1117.1, C1121.1, L1101.2, L1105.1
unnamed: C1112.2, C1114.2, C1118.2, C1122.1, L1102.2, L1106.1
unnamed: C1119.1, L1103.2, L1107.1
unnamed: C1120.2, L1104.2, L1108.1
unnamed: C1121.2, C1123.1, C1127.1, C1132.1, L1105.2, L1109.1
unnamed: C1122.2, C1124.2, C1128.2, C1133.1, L1106.2, L1110.1
unnamed: C1125.1, C1129.1, L1107.2, L1111.1
unnamed: C1126.2, C1130.2, L1108.2, L1112.1
unnamed: C1132.2, C1134.1, C1139.1, C1143.1, L1109.2, L1113.1
unnamed: C1133.2, C1135.2, C1140.2, C1144.1, L1110.2, L1114.1
unnamed: C1136.1, C1141.1, K1102.5, L1111.2, R1115.1, R1118.1
unnamed: C1137.2, C1142.2, K1102.8, L1112.2, R1116.2, R1118.2
unnamed: C1138.2, R1123.2, R1124.1, U1101.1
unnamed: C1143.2, C1146.1, C1148.1, K1102.3, L1113.2, R1119.1, R1126.1
unnamed: C1144.2, C1147.2, C1149.2, K1102.10, L1114.2, R1122.2, R1126.2
unnamed: C1150.1, C1153.1, L1115.1, R1119.2, R1120.1
unnamed: C1151.2, C1154.2, L1116.2, R1121.2, R1122.1
unnamed: C1152.1, R1124.2, R1125.1
unnamed: C1157.2, R1128.1
unnamed: C1159.2, K1102.4, R1129.1
unnamed: C1160.1, K1102.9, R1130.1
unnamed: C1162.1, L1117.2, R1137.2
unnamed: C1163.1, L1118.1, R1136.2
unnamed: C1208.1, C1209.1, L1201.1, R1201.1
unnamed: C1218.2, R1220.1, U1201.7
unnamed: C1220.1, R1222.1, U1203.7
unnamed: C1221.2, R1220.2, R1223.1
unnamed: C1222.1, R1222.2, R1224.1
unnamed: C1310.2, R1317.1, U1301.7
unnamed: C1311.2, R1318.1, U1301.1
unnamed: C1312.1, R1318.2, R1319.2, R1320.1
unnamed: C1316.1, C1317.1, R1322.2
unnamed: C1318.1, L1302.1, R1329.2, R1338.1, R1339.1, R1340.1, R1341.1
unnamed: C1319.1, K1304.4, L1302.2
unnamed: C1320.1, L1303.2, L1304.1
unnamed: C1320.2, R1342.1
unnamed: C1321.2, R1347.1
unnamed: C1327.2, R1372.2, R1377.1, U1303.7
unnamed: D201.1 (K), R202.2
unnamed: D202.1 (K), R203.2
unnamed: D203.1 (K), R204.2
unnamed: D301.2 (A), R311.1, U301.2 (LED2/~INTSEL)
unnamed: D301.1 (K), R313.1
unnamed: D302.2 (A), U301.3 (LED1/REGOFF)
unnamed: D302.1 (K), R314.1
unnamed: D401.2 (A), D402.1 (K), R404.2
unnamed: C612.1, D601.2 (A), L602.2
unnamed: C611.1, D602.2 (A), L601.2
unnamed: C615.1, C617.1, C619.1, D602.1 (K), R606.1, U606.1 (IN)
unnamed: D603.1 (K), F601.1, Q601.3 (S), R605.1, U605.1 (VS)
unnamed: D604.2 (A), R610.2, R611.2
unnamed: D605.2 (A), R611.1
unnamed: C623.1, C624.1, D605.1 (K), L603.2, Q601.2 (D), R610.1, U605.2 (DRAIN)
unnamed: C634.1, D606.2 (A), L605.2
unnamed: C633.1, D607.2 (A), L604.2
unnamed: C635.1, C637.1, C639.1, D607.1 (K), R618.1, U611.1 (IN)
unnamed: D701.1 (K), R707.2
unnamed: D1001.2 (A), U1003.13 (V+)
unnamed: C1216.1, C1221.1, C1224.1, D1201.1 (A), R1214.1, R1229.1
unnamed: C1217.2, C1222.2, C1223.1, D1202.3 (K), R1217.2, R1230.2
unnamed: D1203.2 (A), Q1203.2 (E), R1226.2, R1229.2
unnamed: D1204.1 (K), R1225.2
unnamed: D1205.1, D1206.4, R1228.2
unnamed: C1305.1, D1301.2 (A), D1302.1 (K), R1301.2
unnamed: D1301.3 (K), K1301.9, R1306.1, R1307.1, R1308.1
unnamed: C1306.1, D1301.1 (K), D1303.2 (A), R1302.1
unnamed: D1304.1 (A1), FL1301.3, R1342.2, R1347.2
unnamed: D1305.3 (K), K1304.9, K1305.9, R1361.2, R1369.2
unnamed: D1306.2 (A), K1305.12, Q1301.3 (D)
unnamed: FL1301.4, L1303.1
unnamed: K1301.4, K1301.10
unnamed: K1302.3, R1310.2, R1311.2, R1312.1, R1313.1
unnamed: K1302.4, R1308.2, R1309.2
unnamed: K1302.5, K1302.8
unnamed: K1302.9, K1303.4
unnamed: K1302.10, R1312.2, R1313.2, R1314.1, R1315.1
unnamed: K1303.3, R1323.2, R1324.2, R1326.1, R1327.1
unnamed: K1303.5, K1303.8
unnamed: K1303.9, K1304.5, K1304.10, R1375.1
unnamed: K1303.10, R1326.2, R1327.2, R1330.1, R1331.1, R1332.1, R1333.1
unnamed: K1304.8, R1368.2
unnamed: K1305.10, R1378.1
unnamed: L301.10 (CRX), R320.1
unnamed: L301.15 (CTX), R321.1
unnamed: L301.11 (RX+), U303.1
unnamed: L301.9 (RX-), U303.4
unnamed: L301.16 (TX+), U302.1
unnamed: L301.14 (TX-), U302.4
unnamed: L401.2, R405.2
unnamed: L1202.1, R1221.1
unnamed: L1203.1, R1233.1
unnamed: L1301.1, R1320.2, R1321.2
unnamed: L1301.2, R1322.1, R1325.1
unnamed: Q601.1 (G), U605.3 (GATE)
unnamed: Q1101.1 (B), R1105.2
unnamed: Q1101.2 (E), R1106.2, R1111.2, R1112.1
unnamed: C1216.2, Q1201.1 (D), R1214.2, U1201.5 (+)
unnamed: Q1201.3 (G), R1212.2
unnamed: Q1201.2 (S), R1215.2, U1201.2 (-)
unnamed: Q1202.2 (D), R1208.2, U1203.2 (-)
unnamed: Q1202.3 (G), R1213.2
unnamed: C1217.1, Q1202.1 (S), R1217.1, U1203.5 (+)
unnamed: D1203.3 (K), Q1203.1 (B), R1223.2
unnamed: D1205.3, D1205.4, Q1203.3 (C)
unnamed: D1204.3 (K), Q1204.1 (B), R1224.2
unnamed: D1206.1, D1206.2, Q1204.3 (C)
unnamed: Q1204.2 (E), R1230.1
unnamed: R1007.2, R1008.1, U1001.1
unnamed: R1105.1, U1101.7
unnamed: R1133.2, R1134.2, R1136.1, R1137.1, U1104.6
unnamed: R1205.2, R1206.1, R1209.1, U1202.7
unnamed: R1210.2, R1211.1, U1202.1
unnamed: R1212.1, U1201.1
unnamed: R1213.1, U1203.1
unnamed: R1227.2, R1228.1, U1206.6
unnamed: R1234.2, R1235.1, U1207.6
unnamed: R1306.2, R1309.1
unnamed: R1325.2, R1328.1
unnamed: R1328.2, R1329.1
unnamed: R1343.2, R1348.1, R1349.1, U1304.6
unnamed: R1344.2, R1350.1, R1351.1, U1305.6
unnamed: R1345.2, R1352.1, R1353.1, U1306.6
unnamed: R1346.2, R1354.1, R1355.1, R1358.1, R1370.1, R1371.1, U1307.6
unnamed: R1348.2, R1350.2, R1352.2, R1354.2, R1356.1
unnamed: R1349.2, R1351.2, R1353.2, R1355.2, R1357.1, R1361.1, R1362.1
unnamed: R1356.2, R1359.1
unnamed: R1357.2, R1360.1
unnamed: R1359.2, R1363.1
unnamed: R1360.2, R1364.1
unnamed: R1363.2, R1368.1
unnamed: R1364.2, R1369.1
unnamed: R1379.1, U1302.1, U1302.2, U1302.13, U1302.14
unnamed: R206.2, U201.138 (BOOT0)
unnamed: C209.1, U201.23 (PH0), Y201.1
unnamed: C211.1, U201.24 (PH1), Y201.2
unnamed: R312.2, U301.24 (RBIAS)
unnamed: R303.1, U301.10 (RXER/PHYAD0)
unnamed: C303.1, C306.1, U301.6 (VDDCR)
unnamed: C301.1, U301.5 (XTAL1/CLKIN), Y301.2
unnamed: C304.1, U301.4 (XTAL2), Y301.1
unnamed: U401.13 (B1), U402.3 (VIA)
unnamed: U401.12 (B2), U402.4 (VIB)
unnamed: U401.11 (B3), U402.5 (VOC)
unnamed: R401.2, U401.8 (OE)
unnamed: R402.2, R403.1, U403.2 (D)
unnamed: D401.3 (K), R403.2, R405.1, U403.6 (O), U403.8 (O), U403.11 (O)
unnamed: K501.3, U501.16 (O1)
unnamed: K502.3, U501.15 (O2)
unnamed: K504.3, U501.14 (O3)
unnamed: K503.3, U501.13 (O4)
unnamed: K505.3, U501.12 (O5)
unnamed: K506.3, U501.11 (O6)
unnamed: R601.2, R602.1, U602.4 (EN/UVLO)
unnamed: C615.2, R606.2, R607.1, U602.3 (FBX)
unnamed: C608.1, U602.5 (INTVCC)
unnamed: C611.2, L601.4, U602.1 (SW)
unnamed: R603.2, R604.1, U603.4 (EN/UVLO)
unnamed: C616.2, R608.2, R609.1, U603.3 (FBX)
unnamed: C609.1, U603.5 (INTVCC)
unnamed: C612.2, L602.4, U603.1 (SW)
unnamed: R605.2, U605.6 (ON/~OFF)
unnamed: C616.1, C618.1, C620.1, L602.3, R608.1, U607.2 (VI)
unnamed: R612.2, R613.1, U608.4 (EN/UVLO)
unnamed: C635.2, R618.2, R619.1, U608.3 (FBX)
unnamed: C629.1, U608.5 (INTVCC)
unnamed: C633.2, L604.4, U608.1 (SW)
unnamed: R614.2, R615.1, U609.4 (EN/UVLO)
unnamed: C636.2, R620.2, R621.1, U609.3 (FBX)
unnamed: C630.1, U609.5 (INTVCC)
unnamed: C634.2, L605.4, U609.1 (SW)
unnamed: C631.2, L603.3, U610.1 (+VIN)
unnamed: C632.2, L603.4, U610.2 (-VIN)
unnamed: R616.2, R617.1, U610.4 (TRIM)
unnamed: C636.1, C638.1, C640.1, L605.3, R620.1, U612.2 (VI)
unnamed: R809.1, R811.2, U801.2 (-)
unnamed: R801.1, R803.1, U801.5 (+)
unnamed: R809.2, U801.6 (-), U801.7
unnamed: R810.1, R812.2, U801.9 (-)
unnamed: R802.1, R804.1, U801.12 (+)
unnamed: R810.2, U801.13 (-), U801.14
unnamed: R805.1, R807.1, U802.5 (+)
unnamed: R813.1, R814.1, U802.10 (+)
unnamed: R806.1, R808.1, U802.12 (+)
unnamed: R815.2, R816.2, U803.11 (ADDR)
unnamed: C807.2, R815.1, U803.8 (DECAP)
unnamed: C906.1, R905.2, U901.3 (+)
unnamed: C909.1, R909.2, R910.2, R914.1, U901.2 (-)
unnamed: C907.1, D901.1, D901.3, R908.2, U901.5 (+)
unnamed: C904.1, R904.2, U902.3 (+)
unnamed: C910.1, R911.2, R912.2, R915.1, U902.2 (-)
unnamed: U902.6 (-), U902.7
unnamed: D901.2, D901.4, R906.1, U903.4 (VOUTA)
unnamed: R905.1, U903.13 (VOUTB)
unnamed: D902.1, D902.3, R907.1, U903.5 (VOUTC)
unnamed: R917.1, U903.12 (VOUTD)
unnamed: R904.1, U903.6 (VOUTE)
unnamed: R902.1, U903.11 (VOUTF)
unnamed: R903.1, U903.7 (VOUTG)
unnamed: C901.2, R901.2, U903.8 (VREF)
unnamed: U1001.3 (+), U1003.8 (D)
unnamed: R1006.1, R1007.1, U1001.2 (-)
unnamed: C1009.1, R1011.2, U1001.5 (+)
unnamed: C1006.1, C1008.1, R1012.1, U1001.6 (-), U1001.7
unnamed: C1011.1, C1013.1, U1002.3 (+), U1004.1 (VREF)
unnamed: C1001.1, R1004.2, R1005.1, U1002.6 (-)
unnamed: R1002.2, U1003.2 (EN)
unnamed: D1002.1 (K), U1003.3 (V-)
unnamed: R1013.2, R1014.1, U1004.6 (DATA)
unnamed: C1010.1, R1012.2, U1004.2 (IN+)
unnamed: C1145.1, R1114.2, U1101.3 (+)
unnamed: R1117.2, R1123.1, U1101.2 (-)
unnamed: R1102.2, R1106.1, U1101.6 (-)
unnamed: R1108.2, U1102.18 (FS_ADJ)
unnamed: C1102.1, K1101.4, R1109.1, U1102.22 (IOUTA)
unnamed: C1101.1, K1101.9, R1113.1, U1102.21 (IOUTB)
unnamed: R1107.1, U1102.25 (MODE)
unnamed: C1155.1, C1161.1, L1117.1, U1103.2 (+)
unnamed: C1155.2, C1157.1, R1125.2, R1127.1, U1103.3 (-)
unnamed: R1135.1, U1103.7 (Q)
unnamed: R1127.2, R1128.2, U1103.8 (~Q)
unnamed: R1129.2, R1131.2, R1132.1, U1104.3 (+)
unnamed: R1130.2, R1133.1, R1134.1, U1104.2 (-)
unnamed: C1218.1, R1226.1, U1201.6 (-)
unnamed: R1207.1, U1202.3 (+)
unnamed: R1206.2, R1210.1, U1202.2 (-)
unnamed: L1201.2, R1202.2, R1204.2, U1202.5 (+)
unnamed: R1203.2, R1205.1, U1202.6 (-)
unnamed: C1220.2, R1225.1, U1203.6 (-)
unnamed: U1204.11 (SJ), U1204.13 (IOUT)
unnamed: R1201.2, U1204.9 (VOUT), U1204.10 (RF)
unnamed: C1214.1, R1211.2, U1205.1 (IN0)
unnamed: C1215.1, R1209.2, U1205.3 (IN1)
unnamed: R1218.2, R1219.1, U1205.6 (OUT)
unnamed: R1216.2, U1205.7 (~ENA)
unnamed: C1219.1, R1219.2, U1206.3 (+)
unnamed: R1221.2, R1227.1, U1206.2 (-)
unnamed: C1225.1, C1226.1, D1205.2, D1206.3, R1231.2, U1207.3 (+)
unnamed: R1232.2, R1233.2, R1234.1, U1207.2 (-)
unnamed: C1313.1, R1316.2, R1317.2, R1321.1, U1301.3 (+)
unnamed: C1311.1, R1319.1, U1301.2 (-)
unnamed: C1310.1, R1303.2, R1304.1, R1305.1, R1316.1, U1301.6 (-)
unnamed: R1377.2, U1302.5 (+), U1302.6 (-)
unnamed: C1325.1, R1365.2, R1370.2, R1373.1, U1302.4 (-)
unnamed: C1326.1, R1366.2, R1371.2, R1374.1, U1302.7 (+)
unnamed: R1375.2, R1376.1, U1302.9 (+), U1302.10 (-)
unnamed: U1303.1, U1303.2 (-)
unnamed: C1324.1, R1358.2, R1367.1, U1303.5 (+)
unnamed: C1327.1, R1362.2, R1372.1, U1303.6 (-)
unnamed: R1338.2, U1304.3 (+)
unnamed: R1334.2, R1343.1, U1304.2 (-)
unnamed: R1339.2, U1305.3 (+)
unnamed: R1335.2, R1344.1, U1305.2 (-)
unnamed: R1340.2, U1306.3 (+)
unnamed: R1336.2, R1345.1, U1306.2 (-)
unnamed: R1341.2, U1307.3 (+)
unnamed: R1337.2, R1346.1, U1307.2 (-)
unnamed: R706.1, X701.3 (OUT)
unnamed: R705.2, X701.1 (~ST)
unnamed: R1103.1, R1104.1, X1101.3 (OUT)
unnamed: R1101.2, X1101.1 (~ST)
VCCQ: C307.1, C308.1, C309.1, C310.1, C311.1, C312.1, FB301.1, L301.2 (CTD), L301.7 (CRD), R315.1, R316.1, R317.1, R318.1, U301.1 (VDD2A), U301.19 (VDD1A)
VDDA: C219.1, C220.1, FB201.1, U201.32 (VREF+), U201.33 (VDDA)
VPP: C601.1, C602.1, C603.1, C605.1, C606.1, C610.1, C625.1, C626.1, C627.1, C628.1, C631.1, L601.1, L602.1, L604.1, L605.1, R601.1, R603.1, R612.1, R614.1, R616.1, U601.1 (VI), U602.6 (VIN), U603.6 (VIN), U604.1 (VI), U608.6 (VIN), U609.6 (VIN), U610.3 (+VOUT)
